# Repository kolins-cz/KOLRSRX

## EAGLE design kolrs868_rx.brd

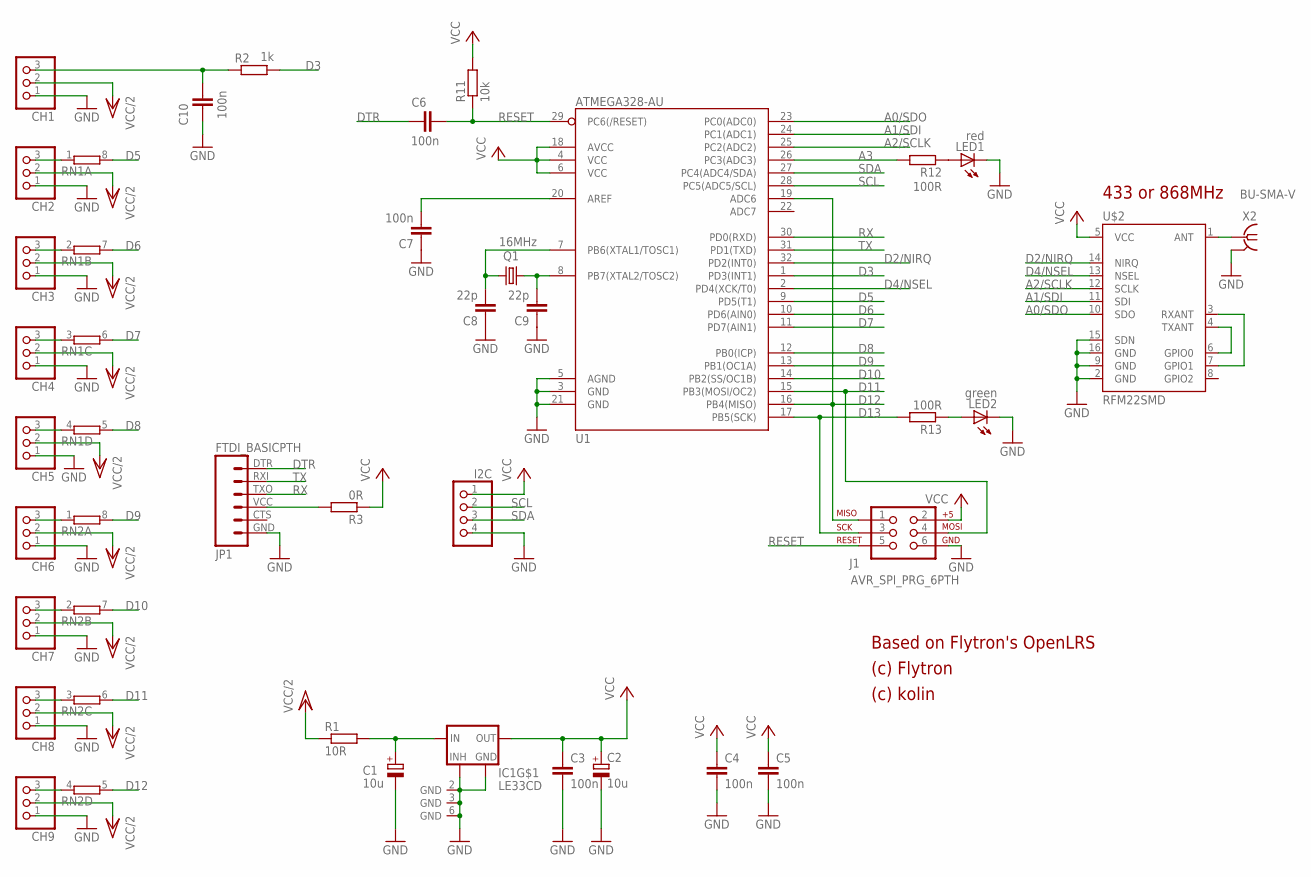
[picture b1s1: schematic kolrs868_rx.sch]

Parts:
C1, C2: 10u; SMC_B
C3, C4, C5, C6, C7, C10: 100n; M0805
C8, C9: 22p; M0805
CH1, CH2, CH3, CH4, CH5, CH6, CH7, CH8, CH9: PINHD-1X3_KOLINOVO; 1X03
I2C: PINHD-1X4; 1X04
IC1: LE33CD; SO8
J1: AVR_SPI_PRG_6PTH; 2X3
JP1: FTDI_BASICPTH; FTDI_BASIC
LED1: red; CHIPLED_0805
LED2: green; CHIPLED_0805
Q1: 16MHz; HC49UP
R1: 10R; M0805
R2: 1k; M0805
R3: 0R; M0805
R11: 10k; M0805
R12, R13: 100R; M0805
RN1, RN2: 4R-NCAY16; CAY16
U1: ATMEGA328-AU; TQFP32-08
U$2: RFM22SMD; RFM22-XXX-S2
X2: BU-SMA-V

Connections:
A0/SDO: U1.23 (PC0(ADC0)), U$2.10 (SDO)
A1/SDI: U1.24 (PC1(ADC1)), U$2.11 (SDI)
A2/SCLK: U1.25 (PC2(ADC2)), U$2.12 (SCLK)
A3: R12.2, U1.26 (PC3(ADC3))
D2/NIRQ: U1.32 (PD2(INT0)), U$2.14 (NIRQ)
D3: R2.2, U1.1 (PD3(INT1))
D4/NSEL: U1.2 (PD4(XCK/T0)), U$2.13 (NSEL)
D5: RN1.8 (2), U1.9 (PD5(T1))
D6: RN1.7 (2), U1.10 (PD6(AIN0))
D7: RN1.6 (2), U1.11 (PD7(AIN1))
D8: RN1.5 (2), U1.12 (PB0(ICP))
D9: RN2.8 (2), U1.13 (PB1(OC1A))
D10: RN2.7 (2), U1.14 (PB2(SS/OC1B))
D11: J1.4, RN2.6 (2), U1.15 (PB3(MOSI/OC2))
D12: J1.1, RN2.5 (2), U1.16 (PB4(MISO)), U1.19 (ADC6)
D13: J1.3, R13.2, U1.17 (PB5(SCK))
DTR: C6.1, JP1.DTR (1)
GND: C1.-, C2.-, C3.2, C4.2, C5.2, C7.1, C8.1, C9.1, C10.1, CH1.1, CH2.1, CH3.1, CH4.1, CH5.1, CH6.1, CH7.1, CH8.1, CH9.1, I2C.4, IC1.2 (GND), IC1.3 (GND), IC1.5 (INHIBIT), IC1.6 (GND), IC1.7 (GND), J1.6, JP1.GND (6), LED1.C, LED2.C, U1.3 (GND), U1.5 (AGND), U1.21 (GND), U$2.2 (GND), U$2.9 (GND), U$2.15 (SDN), U$2.16 (GND), X2.2 (GND), X2.3 (GND), X2.4 (GND), X2.5 (GND)
unnamed: C7.2, U1.20 (AREF)
unnamed: U$2.4 (TXANT), U$2.6 (GPIO0)
unnamed: U$2.3 (RXANT), U$2.7 (GPIO1)
unnamed: U$2.1 (ANT), X2.1
unnamed: LED1.A, R12.1
unnamed: C8.2, Q1.2, U1.7 (PB6(XTAL1/TOSC1))
unnamed: C9.2, Q1.1, U1.8 (PB7(XTAL2/TOSC2))
unnamed: JP1.VCC (4), R3.2
unnamed: C1.+, IC1.8 (IN), R1.2
unnamed: CH5.3, RN1.4 (1)
unnamed: C10.2, CH1.3, R2.1
unnamed: CH2.3, RN1.1
unnamed: CH3.3, RN1.2 (1)
unnamed: CH4.3, RN1.3 (1)
unnamed: CH6.3, RN2.1
unnamed: CH7.3, RN2.2 (1)
unnamed: CH8.3, RN2.3 (1)
unnamed: CH9.3, RN2.4 (1)
unnamed: LED2.A, R13.1
RESET: C6.2, J1.5, R11.1, U1.29 (PC6(/RESET))
RX: JP1.TXO (3), U1.30 (PD0(RXD))
SCL: I2C.2, U1.28 (PC5(ADC5/SCL))
SDA: I2C.3, U1.27 (PC4(ADC4/SDA))
TX: JP1.RXI (2), U1.31 (PD1(TXD))
VCC: C2.+, C3.1, C4.1, C5.1, I2C.1, IC1.1 (OUT), J1.2, R3.1, R11.2, U1.4 (VCC), U1.6 (VCC), U1.18 (AVCC), U$2.5 (VCC)
VCC/2: CH1.2, CH2.2, CH3.2, CH4.2, CH5.2, CH6.2, CH7.2, CH8.2, CH9.2, R1.1

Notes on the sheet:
Based on Flytron's OpenLRS
(c) Flytron
(c) kolin
433 or 868MHz

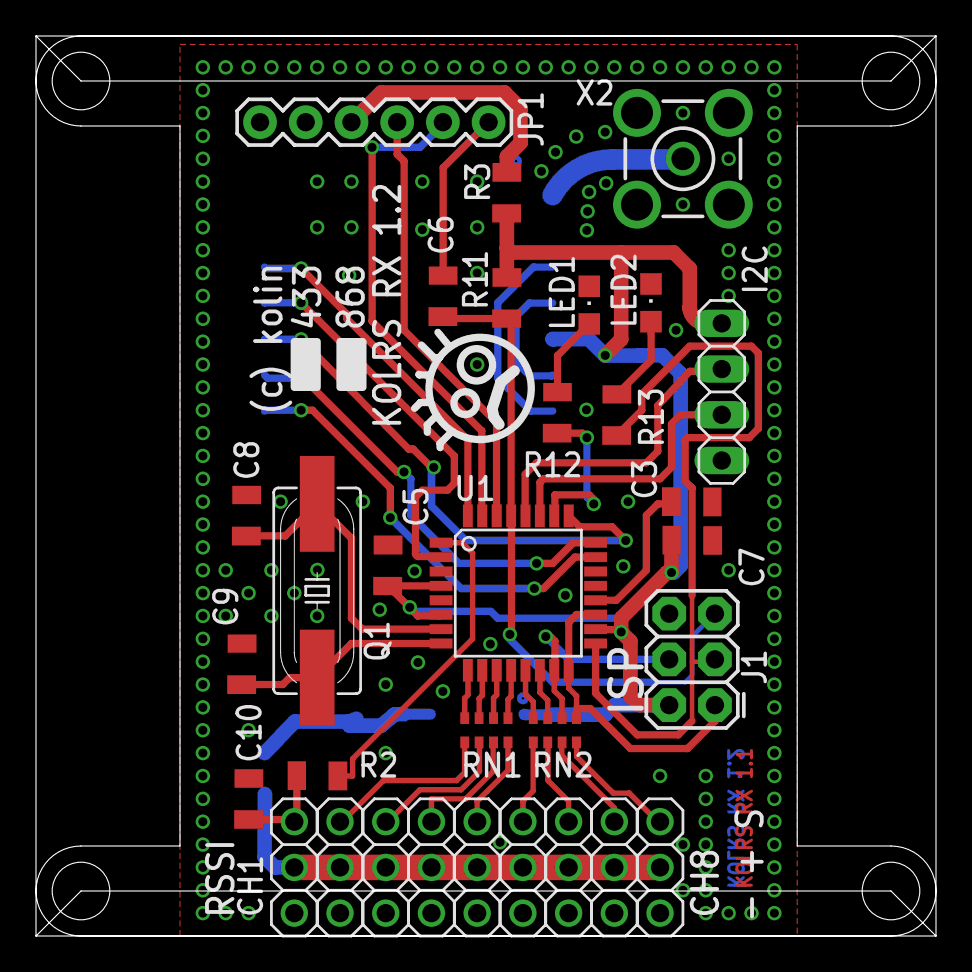
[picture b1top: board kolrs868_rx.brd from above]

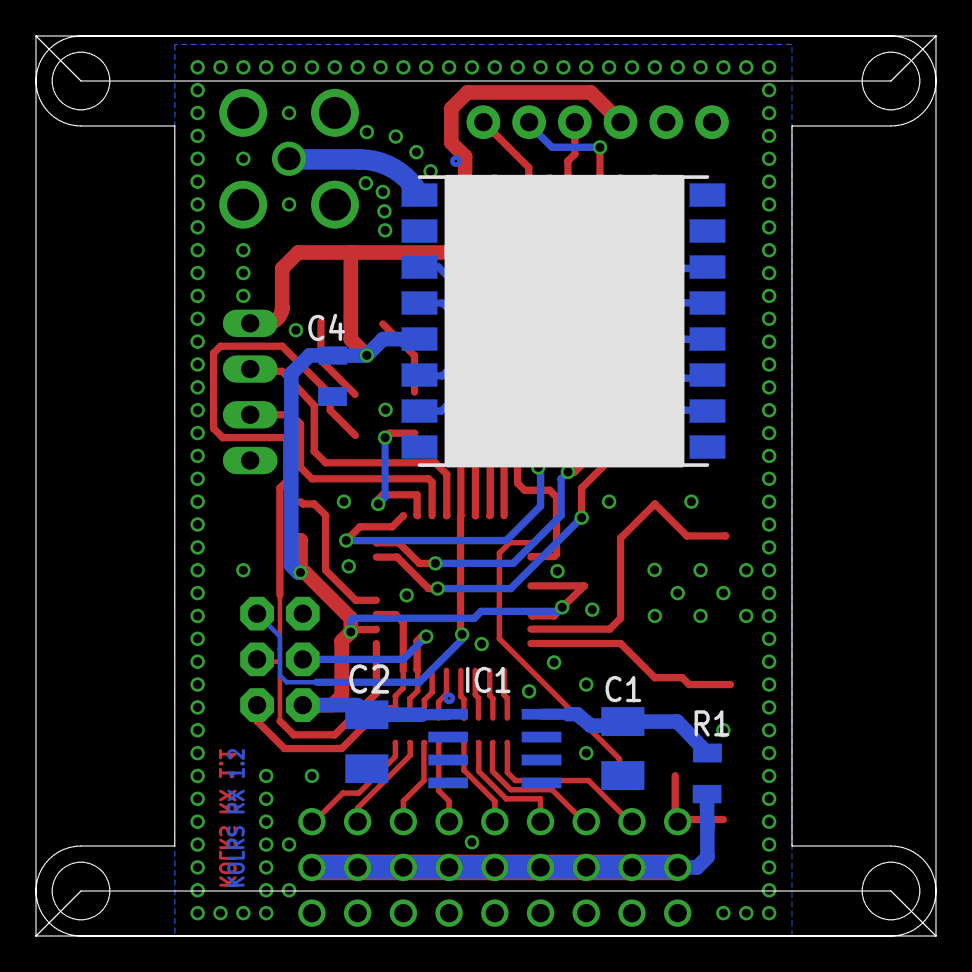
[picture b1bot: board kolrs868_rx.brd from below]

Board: 2 copper layers, 50.0 x 50.0 mm, 37 parts (6 on the bottom side), 44 nets.

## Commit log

2014-08-10 :tada: Added .gitattributes & .gitignore files
2014-08-10 First version
2014-08-10 pokus
2014-08-10 pokus2
